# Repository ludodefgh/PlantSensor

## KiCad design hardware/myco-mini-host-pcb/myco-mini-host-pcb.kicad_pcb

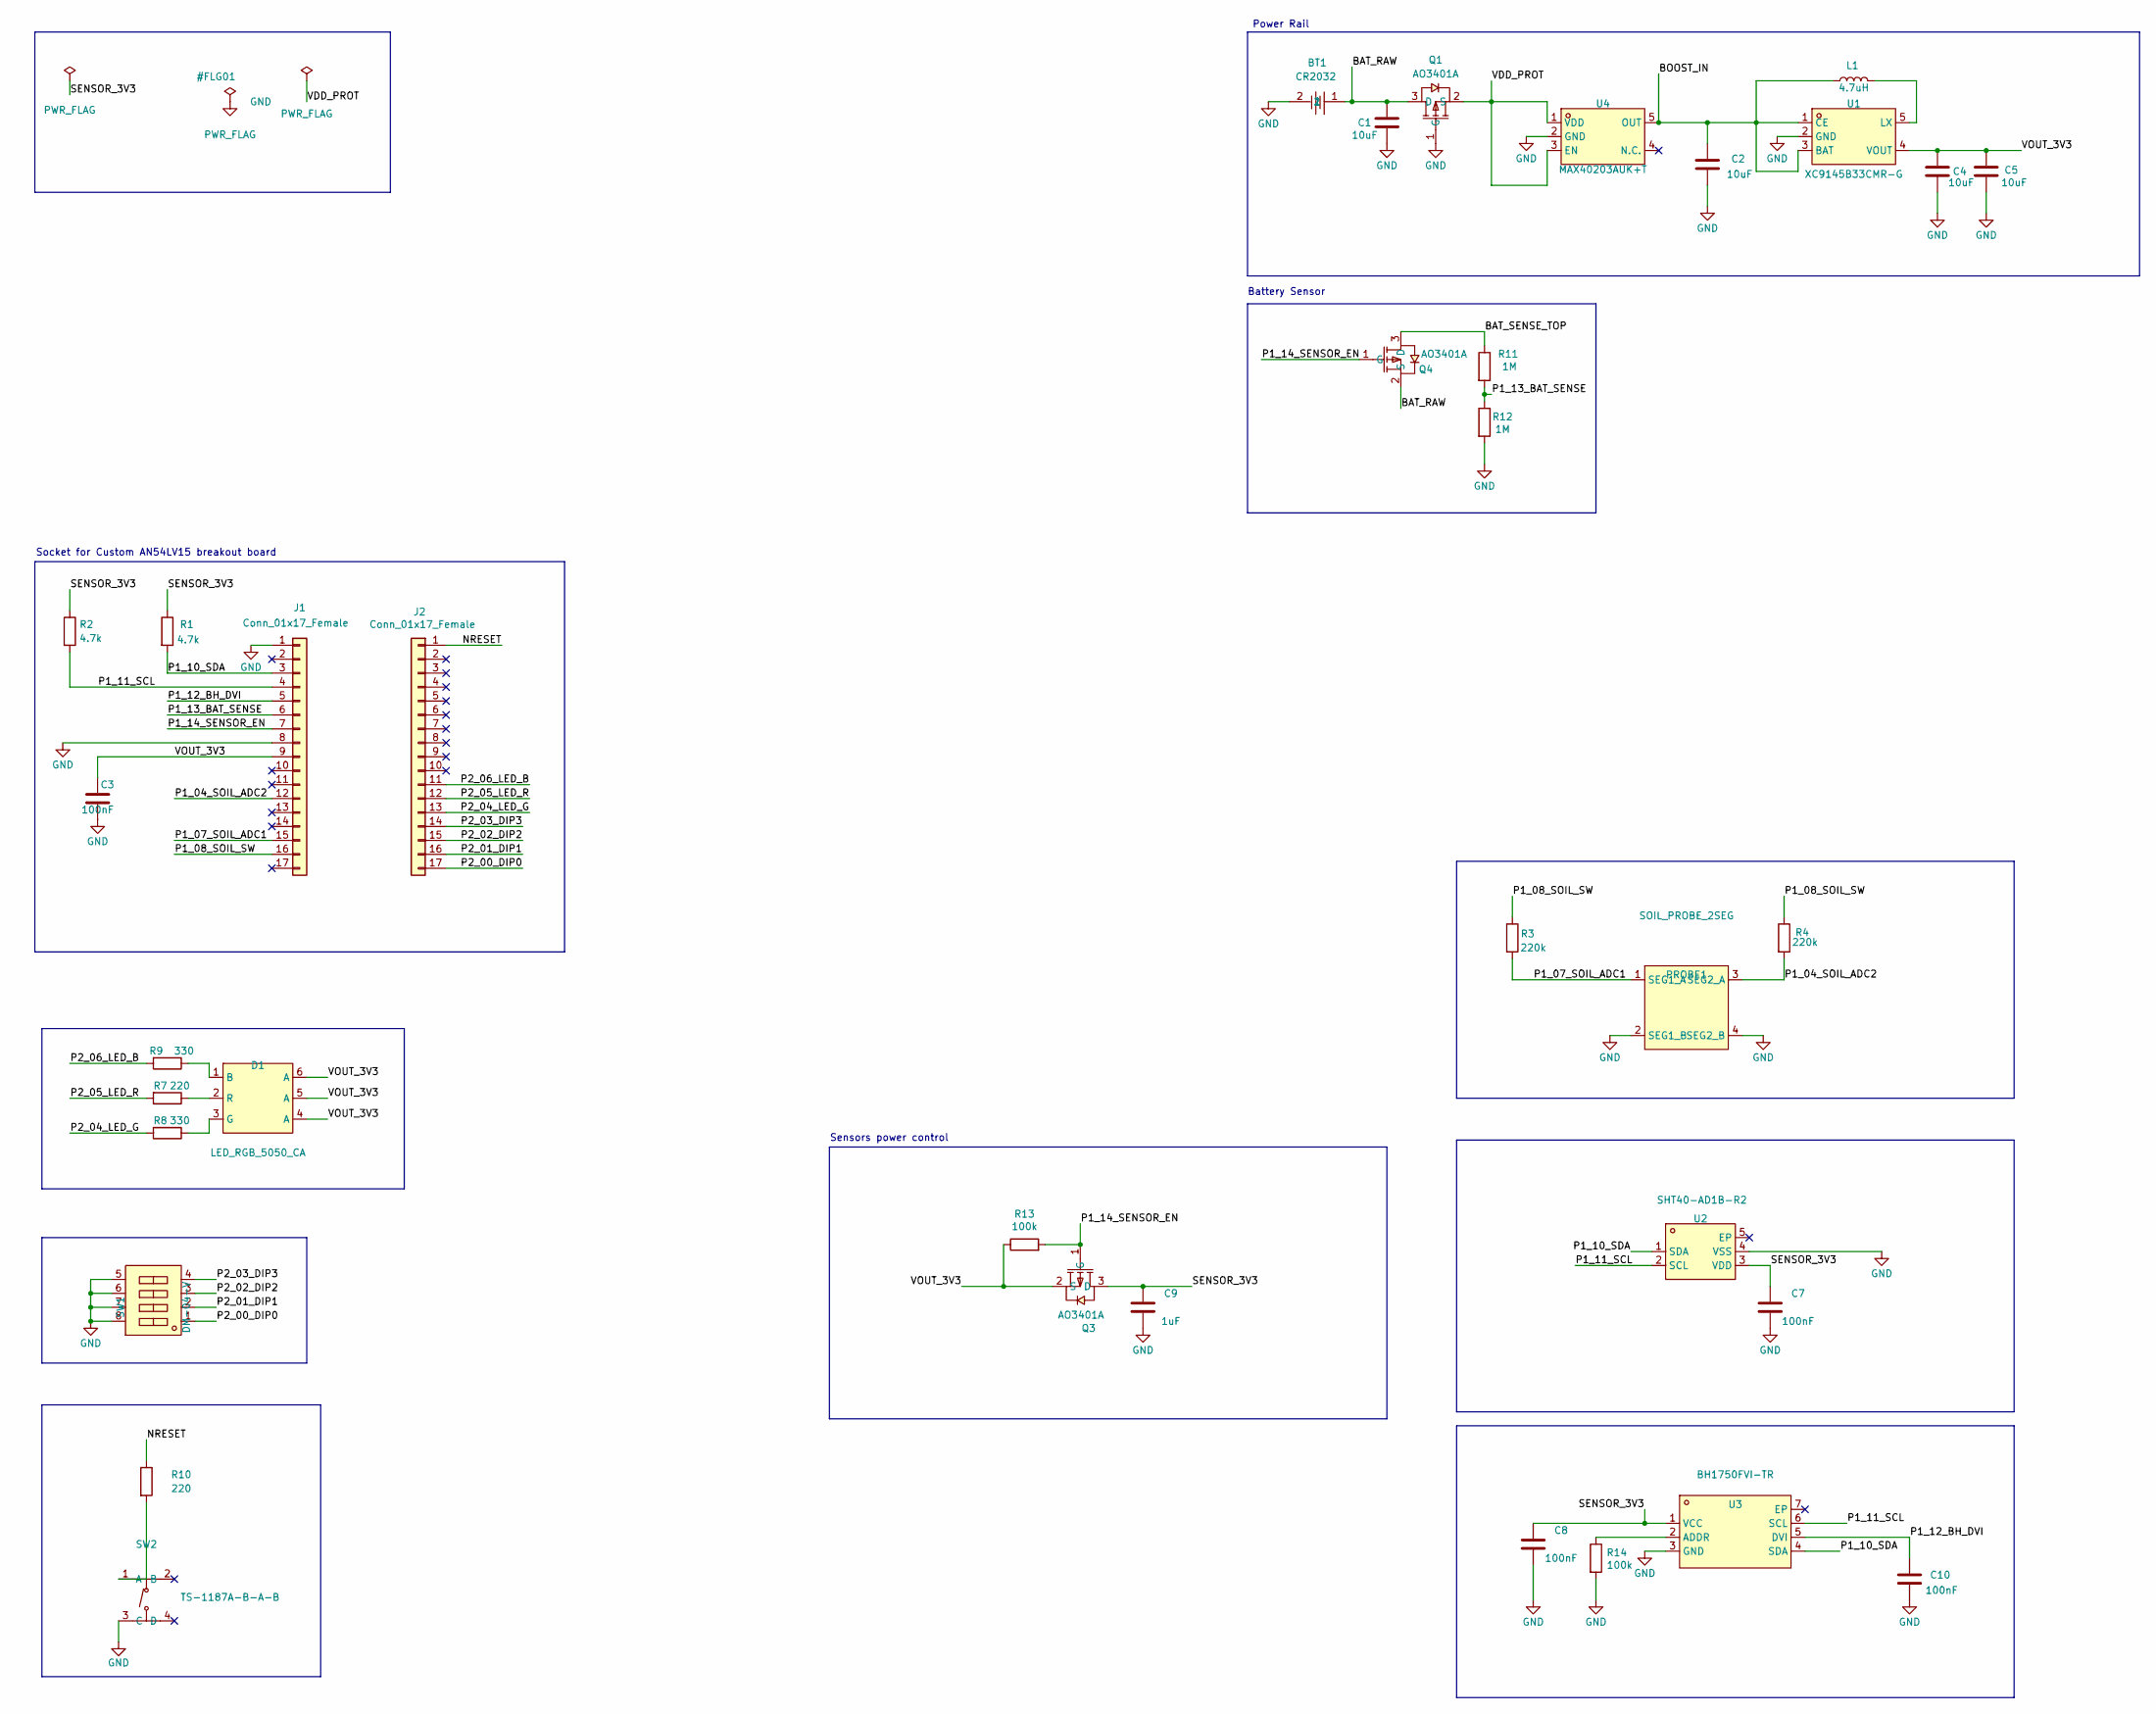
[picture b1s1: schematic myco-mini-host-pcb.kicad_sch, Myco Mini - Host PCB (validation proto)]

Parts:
BT1: CR2032; BAT-TH_CR2032-BS-6-1; LCSC C70377
C1, C2, C4, C5: 10uF; C_0805_2012Metric
C3, C7, C8, C10: 100nF; C_0603_1608Metric
C9: 1uF; C_0603_1608Metric
D1: LED_RGB_5050_CA; LED_SMD5050-6P; LCSC C2843868
J1, J2: Conn_01x17_Female; PinSocket_1x17_P2.54mm_Vertical
L1: 4.7uH; L_1008_2520Metric
PROBE1: SOIL_PROBE_2SEG
Q1, Q3, Q4: AO3401A; SOT-23_L2.9-W1.3-P1.90-LS2.4-BR; LCSC C15127
R1, R2: 4.7k; R_0603_1608Metric
R3, R4: 220k; R_0603_1608Metric
R7, R10: 220; R_0603_1608Metric
R8, R9: 330; R_0603_1608Metric
R11, R12: 1M; R_0603_1608Metric
R13, R14: 100k; R_0603_1608Metric
SW1: DM-04-V; SW-SMD_8P-L11.1-W6.2-P2.54-LS9.8; LCSC C501537
SW2: TS-1187A-B-A-B; SW-SMD_4P-L5.1-W5.1-P3.70-LS6.5-TL_H1.5; LCSC C318884
U1: XC9145B33CMR-G; SOT-25-5_L2.9-W1.6-P0.95-LS2.8-BR; LCSC C19261414
U2: SHT40-AD1B-R2; DFN-4_L1.5-W1.5-P0.8-TL-EP; LCSC C2909890
U3: BH1750FVI-TR; WSOF-6_L2.6-W1.6-P0.50-TL-EP; LCSC C78960
U4: MAX40203AUK+T; SOT-23-5_L3.0-W1.6-P0.95-LS2.8-BR; LCSC C2653639

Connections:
/BAT_RAW: BT1.1, C1.1, Q1.3 (D), Q4.2 (S)
/BAT_SENSE_TOP: Q4.3 (D), R11.1
/BOOST_IN: C2.1, L1.1, U1.1 (CE), U1.3 (BAT), U4.5 (OUT)
/NRESET: J2.1, R10.1
/P1_04_SOIL_ADC2: J1.12, PROBE1.3 (SEG2_A), R4.2
/P1_07_SOIL_ADC1: J1.15, PROBE1.1 (SEG1_A), R3.2
/P1_08_SOIL_SW: J1.16, R3.1, R4.1
/P1_10_SDA: J1.3, R1.2, U2.1 (SDA), U3.4 (SDA)
/P1_11_SCL: J1.4, R2.2, U2.2 (SCL), U3.6 (SCL)
/P1_12_BH_DVI: C10.1, J1.5, U3.5 (DVI)
/P1_13_BAT_SENSE: J1.6, R11.2, R12.1
/P1_14_SENSOR_EN: J1.7, Q3.1 (G), Q4.1 (G), R13.2
/P2_00_DIP0: J2.17, SW1.1
/P2_01_DIP1: J2.16, SW1.2
/P2_02_DIP2: J2.15, SW1.3
/P2_03_DIP3: J2.14, SW1.4
/P2_04_LED_G: J2.13, R8.2
/P2_05_LED_R: J2.12, R7.2
/P2_06_LED_B: J2.11, R9.2
/SENSOR_3V3: C7.1, C8.1, C9.1, Q3.3 (D), R1.1, R2.1, U2.3 (VDD), U3.1 (VCC)
/VDD_PROT: Q1.2 (S), U4.1 (VDD), U4.3 (EN)
/VOUT_3V3: C3.1, C4.1, C5.1, D1.4 (A), D1.5 (A), D1.6 (A), J1.9, Q3.2 (S), R13.1, U1.4 (VOUT)
GND: BT1.2, C1.2, C2.2, C3.2, C4.2, C5.2, C7.2, C8.2, C9.2, C10.2, J1.1, J1.8, PROBE1.2 (SEG1_B), PROBE1.4 (SEG2_B), Q1.1 (G), R12.2, R14.2, SW1.5, SW1.6, SW1.7, SW1.8, SW2.3 (C), U1.2 (GND), U2.4 (VSS), U3.3 (GND), U4.2 (GND)
unnamed: D1.1 (B), R9.1
unnamed: D1.3 (G), R8.1
unnamed: D1.2 (R), R7.1
unnamed: R10.2, SW2.1 (A)
unnamed: L1.2, U1.5 (LX)
unnamed: R14.1, U3.2 (ADDR)

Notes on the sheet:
Socket for Custom AN54LV15 breakout board
Sensors power control
Power Rail
Battery Sensor

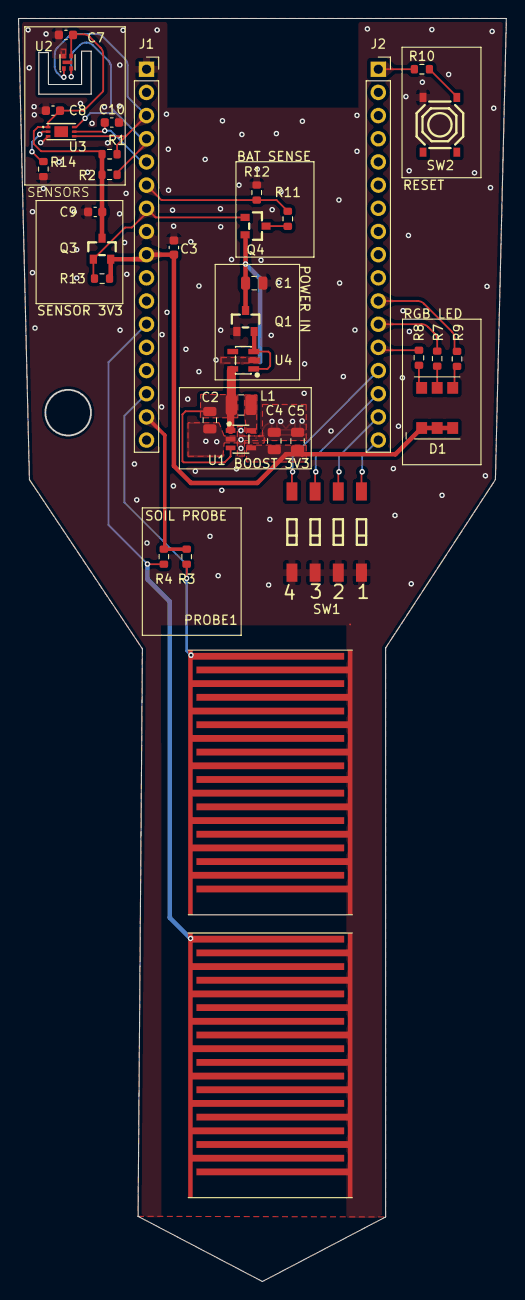
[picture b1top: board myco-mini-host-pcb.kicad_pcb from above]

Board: 2 copper layers, 53.5 x 138.4 mm, 36 parts (1 on the bottom side), 29 nets.

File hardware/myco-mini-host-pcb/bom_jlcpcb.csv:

Comment,Designator,Footprint,LCSC Part #
CR2032,BT1,myco_host:BAT-TH_CR2032-BS-6-1,C70377
10uF,"C1,C2,C4,C5",Capacitor_SMD:C_0805_2012Metric,"C1713 - CL21A106KOQNNNE (Samsung) 10uF 16V X5R 0805 - $0.083/u (MOQ 20, prix verifie LCSC 2026-08-23) - 16V suffisant (rail 3.3V) et moins cher que la version 25V"
Conn_01x17_Female,"J1,J2",Connector_PinSocket_2.54mm:PinSocket_1x17_P2.54mm_Vertical,"N/A - a sourcer separement (LCSC/Digikey), non stocke JLCPCB SMT assembly"
4.7uH,L1,Inductor_SMD:L_1008_2520Metric,"C404806 - TFM252012ALMA4R7MTAA (TDK), boitier ferme/blinde 2.5x2.0x1.2mm identique a l'ancien. $0.3105/u (MOQ 5, prix verifie LCSC 2026-08-24). Remplace MLP2520S4R7ST0S1 (C383386, $0.1095/u) suite a verif contre la page 9 (parts selection guide) du datasheet XC9145 : l'ancien n'avait qu'un rating THERMIQUE 1.0A publie (pas d'Isat), deja sous l'ILIM typ=1.3A du XC9145, et n'etait PAS blindee (datasheet TDK MLP2520 : 'non-magnetic shield type', a l'oppose de la note *5 du XC9145 qui exige un type blinde). Nouveau : Isat max 1.9A / Itemp max 1.6A (marge sur ILIM), circuit magnetique ferme. Footprint KiCad inchange - land pattern TDK verifie quasi-identique entre les deux pieces (span 2.3mm dans les deux cas), et plus genereux que les deux recommandations TDK, donc aucun risque de compatibilite de pads."
SOIL_PROBE_2SEG,PROBE1,myco_host:SOIL_PROBE_2SEG,"N/A - copper PCB pattern uniquement, pas un composant achete"
AO3401A,"Q1,Q3,Q4",myco_host:SOT-23_L2.9-W1.3-P1.90-LS2.4-BR,"C15127 - Q3=sensor VCC switch (VOUT_3V3->SENSOR_3V3), Q4=battery-sense divider switch (BAT_RAW->BAT_SENSE_TOP), both gated by P1_14_SENSOR_EN (J1 pin 7). Q2 (soil probe switch) supprime : P1.08 attaque R3/R4 directement, voir issue #20."
4.7k,"R1,R2",Resistor_SMD:R_0603_1608Metric,"C23162 - 0603WAF4701T5E (UNI-ROYAL) 4.7k 1% 0603 - $0.0030/u (MOQ 100, prix verifie LCSC 2026-08-23) - pull-ups I2C sur SENSOR_3V3"
220k,"R3,R4",Resistor_SMD:R_0603_1608Metric,"C22961 - 0603WAF2203T5E (UNI-ROYAL) 220k 1% 0603 - $0.0025/u (MOQ 100, prix verifie LCSC 2026-08-23) - resistances RC de la sonde sol"
100k,"R13,R14",Resistor_SMD:R_0603_1608Metric,"C25803 - 0603WAF1003T5E (UNI-ROYAL) 100k 1% 0603 - $0.0042/u (MOQ 100, prix verifie LCSC 2026-08-23) - R13=pull-up gate Q3/Q4, R14=pull-down ADDR BH1750. R5 (pull-up gate Q2) supprime avec Q2, voir issue #20."
DM-04-V,SW1,myco_host:SW-SMD_8P-L11.1-W6.2-P2.54-LS9.8,"C501537 - remplace EM-04-Q (C501635, rupture de stock au 2026-08-22), meme fabricant Diptronics, meme pairing electrique, footprint tourne 90deg"
XC9145B33CMR-G,U1,myco_host:SOT-25-5_L2.9-W1.6-P0.95-LS2.8-BR,C19261414
SHT40-AD1B-R2,U2,myco_host:DFN-4_L1.5-W1.5-P0.8-TL-EP,"C2909890 - Extended part, en stock LCSC/JLCPCB (~9000 pieces au 2026-08-24), ~$1.79/u a l'unite et ~$1.14/u a 1000+. Remplace SHT41-AD1B-R2 (C7461861), qui n'etait PAS reference sur LCSC et devait etre source separement chez Digikey (~$6.95/u). Meme boitier DFN-4 1.5x1.5mm, meme pinout, meme adresse I2C 0x44 - aucun impact footprint/layout. Contrepartie acceptee : +-3%RH au lieu de +-2%RH aux extremes 0-10%RH et 90-100%RH (les deux parts sont a +-1.8%RH sur 20-80%RH). Assemblage hotplate par l'utilisateur."
BH1750FVI-TR,U3,myco_host:WSOF-6_L2.6-W1.6-P0.50-TL-EP,C78960
XL-5050RGBC,D1,myco_host:LED_SMD5050-6P,"C2843868 - pinout verified vs Xinglight datasheet; G/B channels marginal Vf headroom on 3.3V rail, see decision log 2.10"
220,"R7,R10",Resistor_SMD:R_0603_1608Metric,"C22962 - 0603WAF2200T5E (UNI-ROYAL) 220R 1% 0603 - $0.0086/u (MOQ 100, prix verifie LCSC 2026-08-23) - R7=serie LED rouge, R10=serie bouton reset"
330,"R8,R9",Resistor_SMD:R_0603_1608Metric,"C23138 - 0603WAF3300T5E (UNI-ROYAL) 330R 1% 0603 - $0.0043/u (MOQ 100, prix verifie LCSC 2026-08-23)"
MAX40203AUK+T,U4,myco_host:SOT-23-5_L3.0-W1.6-P0.95-LS2.8-BR,"C2653639 - ideal diode, blocks backfeed from breakout J5/Pico-probe into BAT_RAW, voir decision log"
TS-1187A-B-A-B,SW2,myco_host:SW-SMD_4P-L5.1-W5.1-P3.70-LS6.5-TL_H1.5,"C318884 - bouton reset, NRESET (J2 pin1) -> R10 -> SW2 -> GND"
1M,"R11,R12",Resistor_SMD:R_0603_1608Metric,"C22935 - 0603WAF1004T5E (UNI-ROYAL) 1M 1% 0603 - $0.0028/u (MOQ 100, prix verifie LCSC 2026-08-23) - diviseur mesure batterie 2:1 vers P1_13_BAT_SENSE (J1 pin 6, AIN6)"
100nF,"C3,C7,C8,C10",Capacitor_SMD:C_0603_1608Metric,"C14663 - CC0603KRX7R9BB104 (YAGEO) 100nF 50V X7R 0603 - $0.0151/u (MOQ 50, prix verifie LCSC 2026-08-23) - C3=bypass HF pres de J1 pin9 ; C7/C8=decouplage SENSOR_3V3 au plus pres de U2/U3 ; C10=decouplage DVI du BH1750 (montage ex1 du datasheet ROHM, DVI pilote par P1.12), voir issue #21."
1uF,C9,Capacitor_SMD:C_0603_1608Metric,"C157684 - 0603X105K500NT (FH) 1uF 50V X5R 0603 - $0.0171/u (MOQ 50, prix verifie LCSC 2026-08-26) - remplace C15849 (Samsung CL10A105KB8NNNC), en rupture de stock au 2026-08-26 (stockNumber=0). Meme spec exacte : 1uF, 50V, X5R, 0603."

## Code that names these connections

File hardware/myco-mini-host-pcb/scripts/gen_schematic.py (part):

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            bt1_x, bt1_y, footprint="myco_host:BAT-TH_CR2032-BS-6-1",
            extra_props={"LCSC": "C70377"})
# pin1 = BAT+ (assumed, verify vs datasheet), pin2 = BAT- (assumed)
stub_and_label(bt1["1"], "BAT_RAW")
stub_and_gnd(bt1["2"])
pf = place(PARTS['PWRFLAG'], "#FLG01", "PWR_FLAG", bt1_x, bt1_y + 15, in_bom=False)
place_gnd(pf["1"][0], pf["1"][1])

c1_x, c1_y = 150, 40
c1 = place(PARTS['C'], "C1", "10uF", c1_x, c1_y, footprint="Capacitor_SMD:C_0805_2012Metric")
stub_and_label(c1["1"], "BAT_RAW", label_angle=180)
stub_and_gnd(c1["2"])

q1_x, q1_y = 175, 45
q1 = place(PARTS['AO3401'], "Q1", "AO3401A", q1_x, q1_y,
           footprint="myco_host:SOT-23_L2.9-W1.3-P1.90-LS2.4-BR",
           extra_props={"LCSC": "C15127", "Note": "Reverse polarity protect: S=BAT_RAW D=VDD_NRF G=GND"})
stub_and_label(q1["S"], "BAT_RAW")
stub_and_label(q1["D"], "VDD_NRF")
stub_and_gnd(q1["G"])

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wire_direct((lx_pin[0], lx_pin[1]), (l1["2"][0], l1["2"][1]))
NETLIST.append((lx_pin[4], lx_pin[5], "LX_NODE"))
NETLIST.append((l1["2"][4], l1["2"][5], "LX_NODE"))
stub_and_label(u1["VOUT"], "VOUT_3V3")

r6_x, r6_y = 250, 70
r6 = place(PARTS['R'], "R6", "100k", r6_x, r6_y, footprint="Resistor_SMD:R_0603_1608Metric",
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
c4_x, c4_y = 280, 40
c4 = place(PARTS['C'], "C4", "10uF", c4_x, c4_y, footprint="Capacitor_SMD:C_0805_2012Metric")
stub_and_label(c4["1"], "VOUT_3V3", label_angle=180)
stub_and_gnd(c4["2"])

c5_x, c5_y = 300, 40
c5 = place(PARTS['C'], "C5", "10uF", c5_x, c5_y, footprint="Capacitor_SMD:C_0805_2012Metric")
stub_and_label(c5["1"], "VOUT_3V3", label_angle=180)
stub_and_gnd(c5["2"])

# --- Soil VCC switch ---
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q2 = place(PARTS['AO3401'], "Q2", "AO3401A", q2_x, q2_y,
           footprint="myco_host:SOT-23_L2.9-W1.3-P1.90-LS2.4-BR",
           extra_props={"LCSC": "C15127", "Note": "Soil probe VCC switch: S=VOUT_3V3 D=SOIL_VCC G=P1_14"})
stub_and_label(q2["S"], "VOUT_3V3")
stub_and_label(q2["D"], "SOIL_VCC")
stub_and_label(q2["G"], "P1_14_SOIL_SW")

r5_x, r5_y = 330, 70
r5 = place(PARTS['R'], "R5", "100k", r5_x, r5_y, footprint="Resistor_SMD:R_0603_1608Metric",
           extra_props={"Note": "Gate pull-up, default-off before GPIO init"})
stub_and_label(r5["1"], "VOUT_3V3")
stub_and_label(r5["2"], "P1_14_SOIL_SW")

# --- Sensors ---
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           extra_props={"LCSC": "C7461861", "Note": "Same package/pinout as SHT40, better RH accuracy at extremes - see decision log"})
stub_and_label(u2["SDA"], "P0_02_SDA", label_angle=180)
stub_and_label(u2["SCL"], "P0_03_SCL", label_angle=180)
stub_and_label(u2["VDD"], "VOUT_3V3")
stub_and_gnd(u2["VSS"])
stub_and_gnd(u2["EP"])

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u3 = place(PARTS['BH1750'], "U3", "BH1750FVI-TR", u3_x, u3_y,
           footprint="myco_host:WSOF-6_L2.6-W1.6-P0.50-TL-EP",
           extra_props={"LCSC": "C78960", "Note": "ADDR=GND -> I2C addr 0x23"})
stub_and_label(u3["VCC"], "VOUT_3V3", label_angle=180)
stub_and_gnd(u3["ADDR"])
stub_and_gnd(u3["GND"])
stub_and_label(u3["SDA"], "P0_02_SDA")
stub_and_label(u3["DVI"], "VOUT_3V3")
stub_and_label(u3["SCL"], "P0_03_SCL")
stub_and_gnd(u3["EP"])

r1_x, r1_y = 130, 100
r1 = place(PARTS['R'], "R1", "4.7k", r1_x, r1_y, footprint="Resistor_SMD:R_0603_1608Metric",
           extra_props={"Note": "I2C SDA pull-up - moved to VOUT_3V3, see decision log 2.5ter (both I2C devices now on switched rail)"})
stub_and_label(r1["1"], "VOUT_3V3")
stub_and_label(r1["2"], "P0_02_SDA")

r2_x, r2_y = 150, 100
r2 = place(PARTS['R'], "R2", "4.7k", r2_x, r2_y, footprint="Resistor_SMD:R_0603_1608Metric",
           extra_props={"Note": "I2C SCL pull-up - moved to VOUT_3V3, see decision log 2.5ter (both I2C devices now on switched rail)"})
stub_and_label(r2["1"], "VOUT_3V3")
stub_and_label(r2["2"], "P0_03_SCL")

# --- Soil probe ---
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probe = place(PARTS['PROBE'], "PROBE1", "SOIL_PROBE_2SEG",
              probe_x, probe_y, footprint="myco_host:SOIL_PROBE_2SEG",
              extra_props={"Note": "PCB copper only - straight interdigitated comb, see decision log"})
stub_and_label(probe["1"], "P1_07_SOIL_ADC1", label_angle=180)  # SEG1_A
stub_and_gnd(probe["2"])                                        # SEG1_B
stub_and_label(probe["3"], "P1_04_SOIL_ADC2")                    # SEG2_A
stub_and_gnd(probe["4"])                                         # SEG2_B

r3_x, r3_y = 300, 130
r3 = place(PARTS['R'], "R3", "220k", r3_x, r3_y, footprint="Resistor_SMD:R_0603_1608Metric",
           extra_props={"Note": "Bias resistor, segment 1 - lowered from 1M, see decision log 2.6"})
stub_and_label(r3["1"], "SOIL_VCC")
stub_and_label(r3["2"], "P1_07_SOIL_ADC1")

r4_x, r4_y = 300, 170
r4 = place(PARTS['R'], "R4", "220k", r4_x, r4_y, footprint="Resistor_SMD:R_0603_1608Metric",
           extra_props={"Note": "Bias resistor, segment 2 - lowered from 1M, see decision log 2.6"})
stub_and_label(r4["1"], "SOIL_VCC")
stub_and_label(r4["2"], "P1_04_SOIL_ADC2")

# --- DIP switches ---
sw1_x, sw1_y = 430, 190
sw1 = place(PARTS['DIPSW'], "SW1", "EM-04-Q", sw1_x, sw1_y,
            footprint="myco_host:SW-SMD_8P-L10.1-W6.0-P2.54-LS9.8",
            extra_props={"LCSC": "C501635", "Note": "Pin pairing 1-8,2-7,3-6,4-5 verified from EasyEDA symbol geometry"})
stub_and_label(sw1["1"], "P2_00_DIP0", stub_len=3.81)
stub_and_label(sw1["2"], "P2_01_DIP1", stub_len=7.62)
stub_and_label(sw1["3"], "P2_02_DIP2", stub_len=11.43)
stub_and_label(sw1["4"], "P2_03_DIP3", stub_len=15.24)
for n in ["5", "6", "7", "8"]:
    stub_and_gnd(sw1[n])

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
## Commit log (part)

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2026-03-13 "Add nRF54L15 DeviceTree - pinout final Myco Mini"
